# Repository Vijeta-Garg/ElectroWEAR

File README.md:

# ElectroWEAR

Inspiration: 
I've been working on an electropneumatically powered mechanotherapy wearable for breast cancer survivors, including in my last iteration (link to that abstract is here: https://www.overleaf.com/read/rxshvgcpytvv#2f1c8a in which I created custom soft actuator structures for this application). However, the last electropneumatic system I made was powered by a 12 Volt battery + hard to integrate into a wearable. I wanted to make an electropneumatic system that can be easier to integrate into a mechanotherapy vest for breast cancer survivors.

What the project does:
The project uses 6 Volts (unlike the earlier iterations which used 12Volts) and smaller components to make the electropneumatic as compact as possible so that it can  be integrated into a garment.

How it works:
A 6V battery powers the circuit while an Arduino Uno relays commands of which component should be on/off according to the code on the Arduino IDE. TIP120 and 1N4007 are there to primarily regulate electrical flow. This circuit powers 2 air pumps/compressors and 2 solenoid valves (although it can be adjusted to power just one of each as was done in this wearable). Furthermore, the circuit is electropneumatic, and it contains a "pneumatic" component in the way the air pumps and solenoid valves are conntected to each other through plastic piping and finally connected to the actuator. This part of the circuit maintains pneumatic flow and allows solenoid valves and air pumps to act as both inlets and outlets (if more than one is used). 

An example of the before and after:

**Before**

**Now: ElectroWEAR**

# Schematic 
This is the wiring diagram/schematic. This includes both the electrical parts of the circuit (contained in the "main circuit board") and the pneumatic parts of the circuit (which are integrated across the wearable rather than in the gray pocket on the bottom-left)!

# Layout 
This is how the circuit is mapped out onto the wearable. Currently the main "control board" is only breadboarded and not PCBed but the files are ready and I just need to order the PCB and substitute it in (that is why that box says breadboard/perfboard/PCB) 
Also note: if one was to wear ElectroWEAR the battery component would theoretically live in their pant pocket or a string bag. 

# PCB (and maybe CAD) 

# How to build this? 
1. Wire up the main electrical component (refer to the schematic in pcb folder). Every solenoid valve or air pump added require the same subset of wiring: TIP120 connected to 1N4007 diode and also connected to the component and GND and Power rails.
2. Connect this circuit to the 6V battery holder. Put the 1.5V batteries inside this battery holder. Remember NOT to plug the 6V directly into the arduino! Plug into power rail to share with components! Either connect by soldering or alligator clips! 
3. Import firmware to arduino IDE and run the circuit
4. Build out the pneumatic section of the circuit by using the schematic as reference. The joint parts are all pneumatic connectors *which look like pipes. Test the circuit out with the pneumatic connections as well. Get pneumatic connectors (plastic tubes) to connect the pipes 
5. Cut out 4 different pockets (preferably of strong material like denim) on a shirt and place the circuit as detailed in the layout diagram. If you have a soft textile actuator (or any output you want the electropneumatic to puff up) place that in the top-left pocket) 
6. Sew the pockets closed and the build is done!
7. Print out the flex PCB design detailed in this repo. Then, unsew the controller pocket and connect that to the arduino + into the pocket instead of the earlier perfboarded/breadboarded version!

# BOM (properly formatted in the bom.csv file in the repo) 
Please note: I don't need reimbursement for any of these materials since I can use research grant money I've gotten for this project!

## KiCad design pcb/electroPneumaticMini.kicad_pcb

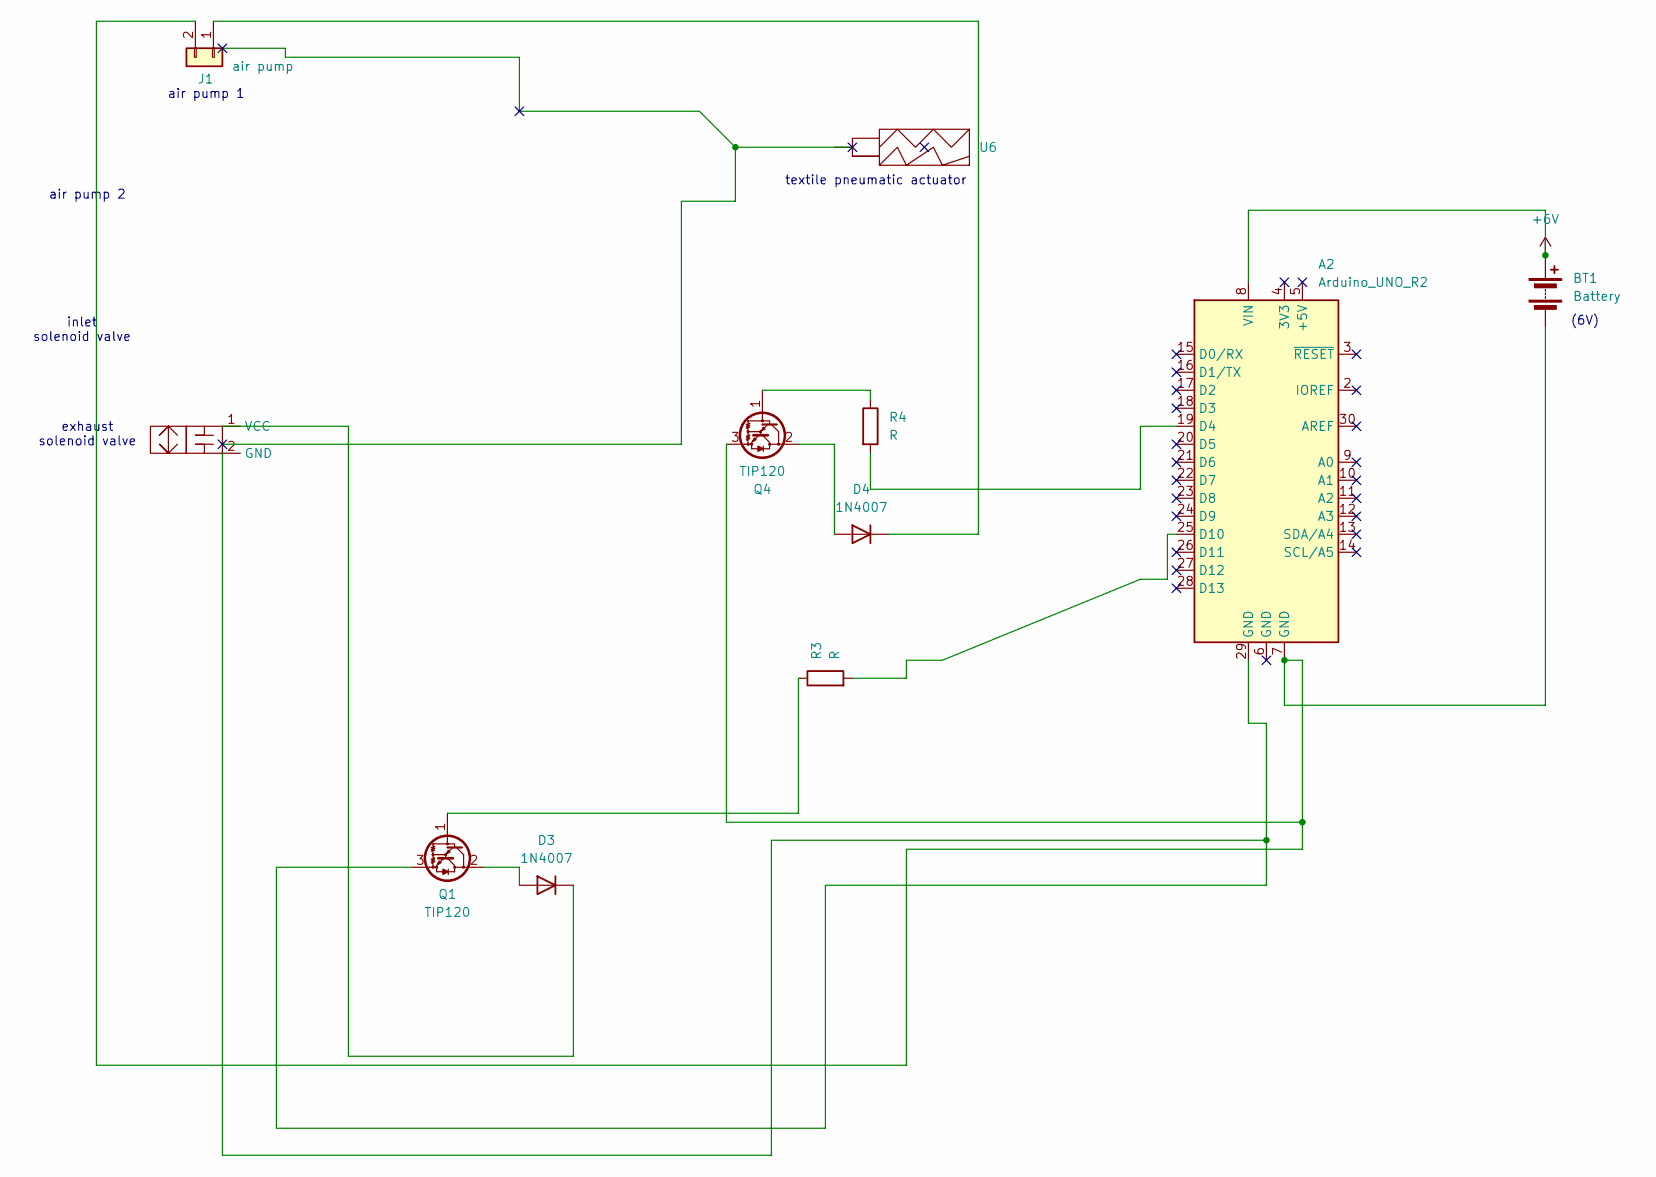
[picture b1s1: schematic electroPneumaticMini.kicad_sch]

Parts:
A2: Arduino_UNO_R2
BT1: Battery; PinHeader_1x02_P2.54mm_Vertical
D3, D4: 1N4007; D_DO-41_SOD81_P10.16mm_Horizontal
J1: air pump; PinHeader_1x02_P1.00mm_Vertical
Q1, Q4: TIP120; TO-220-3_Vertical
R3, R4: R; R_Axial_DIN0204_L3.6mm_D1.6mm_P7.62mm_Horizontal
U6: (no value)
u5: PinHeader_1x02_P2.54mm_Vertical

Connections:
+6V: A2.8 (VIN), BT1.1 (+)
unnamed: A2.19 (D4), R4.2
unnamed: A2.25 (D10), R3.2
unnamed: A2.7 (GND), BT1.2 (-), J1.2, Q4.3 (E)
unnamed: D3.2 (A), Q1.2 (C)
unnamed: D3.1 (K), u5.1 (VCC)
unnamed: D4.2 (A), Q4.2 (C)
unnamed: D4.1 (K), J1.1
unnamed: Q1.1 (B), R3.1
unnamed: A2.29 (GND), Q1.3 (E), u5.2 (GND)
unnamed: Q4.1 (B), R4.1

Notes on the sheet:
air pump 1
air pump 2
(6V)
inlet solenoid valve
textile pneumatic actuator
exhaust solenoid valve

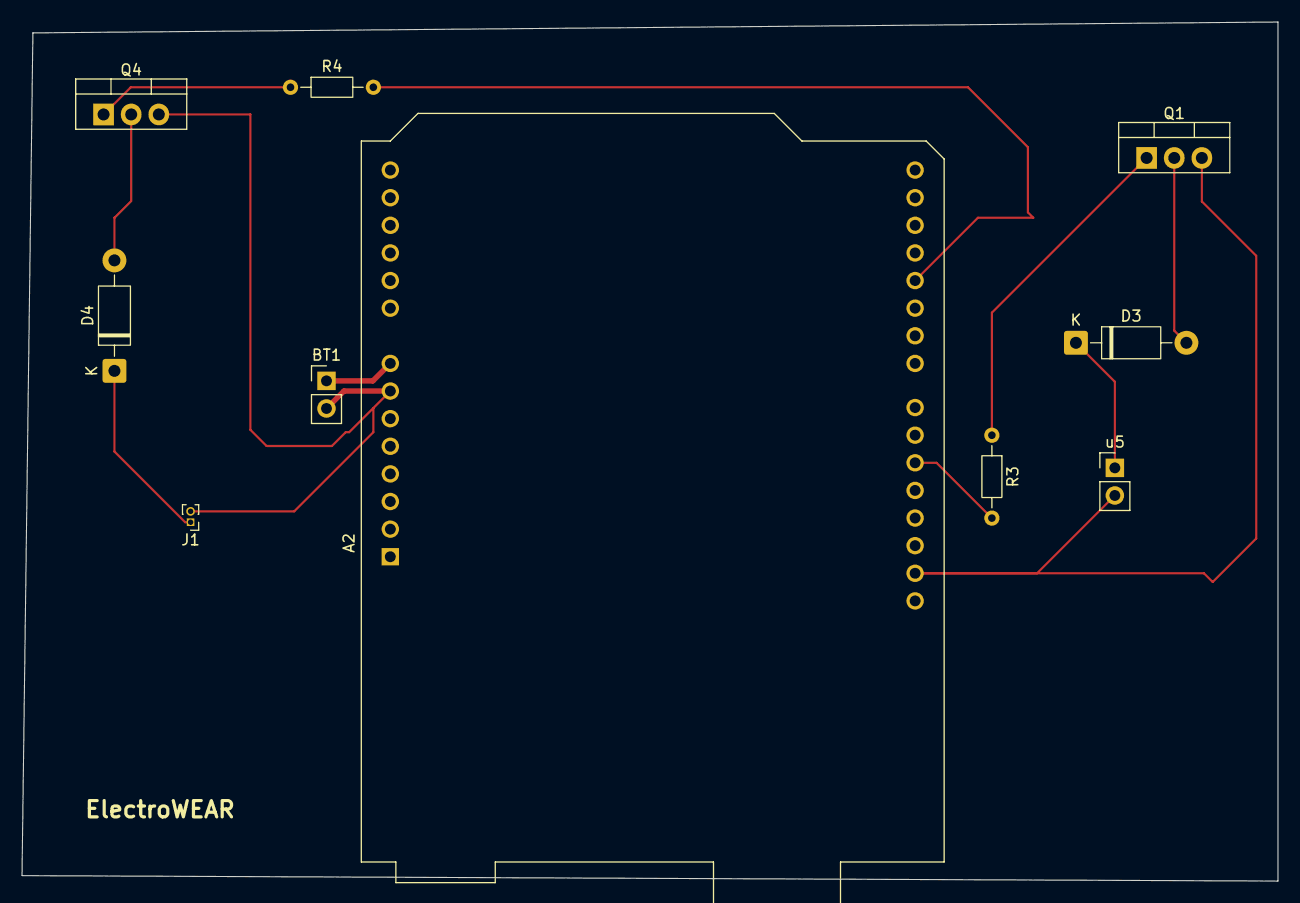
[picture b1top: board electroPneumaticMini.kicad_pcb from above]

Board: 2 copper layers, 115.5 x 79.0 mm, 10 parts (0 on the bottom side), 11 nets.

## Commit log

2026-06-20 Revise README for ElectroWEAR project details
    Updated project description and details about the electropneumatic system for better clarity and integration into a wearable.
2026-06-25 Update BOM.csv with structured item details
2026-06-25 Update README with BOM details and funding note
    Added BOM section and clarified funding for materials.
2026-06-25 Update BOM.csv with corrected entries
    Corrected item quantities and prices, and updated URLs.
2026-06-25 Update image in README.md
    Replaced an image in the README with a new one.
2026-06-26 Update README with battery component location details
    Added note about battery component placement for ElectroWEAR.
2026-06-27 Create hello
